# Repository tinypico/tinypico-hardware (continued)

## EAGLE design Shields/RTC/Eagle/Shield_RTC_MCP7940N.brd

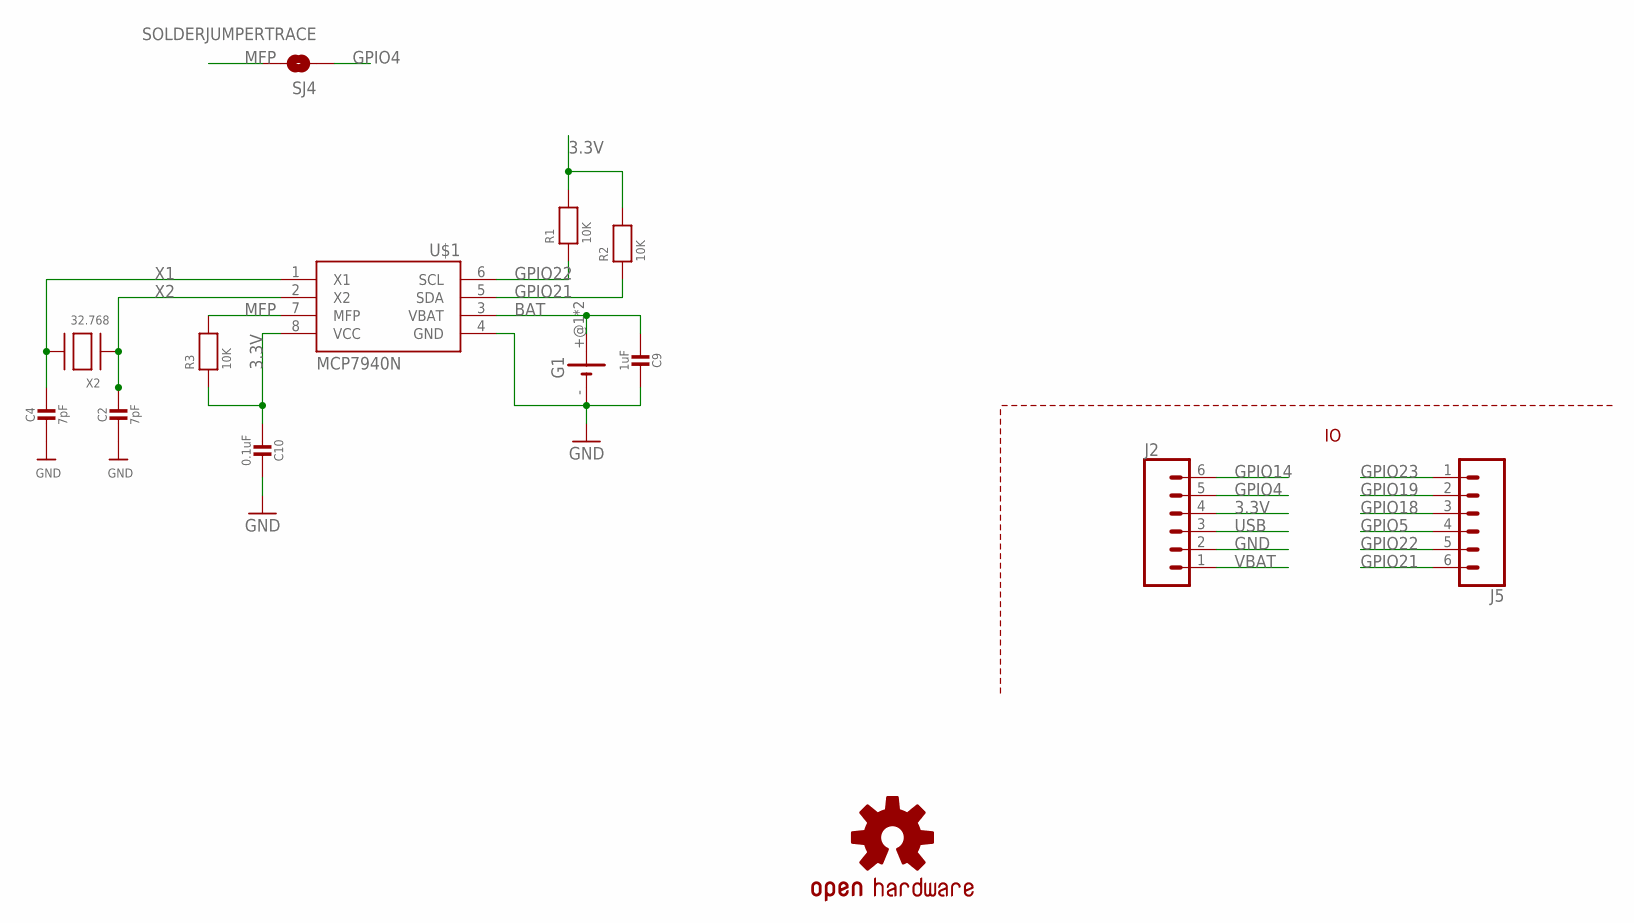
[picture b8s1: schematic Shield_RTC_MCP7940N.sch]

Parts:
C2, C4: 7pF; _0603MP
C9: 1uF; _0603MP
C10: 0.1uF; _0603MP
G1: 10MM_SM_COIN_CELL_CLIP
J2, J5: CONN_06NO_SILK_FEMALE_PTH; 1X06_NO_SILK
LOGO1: OSHW-LOGOS; OSHW-LOGO-S
R1, R2, R3: 10K; _0603MP
SJ4: SOLDERJUMPERTRACE; SPARKFUN_SJ_2S-TRACE
U$1: MCP7940N; SOIC8_150MIL
X2: 32.768; XTAL3215

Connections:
3.3V: C10.2, J2.4, R1.2, R2.2, R3.1, U$1.8 (VCC)
BAT: C9.2, G1.+@1 (+), G1.+@2 (+), U$1.3 (VBAT)
GND: C2.2, C4.2, C9.1, C10.1, G1.-, J2.2, U$1.4 (GND)
GPIO4: J2.5, SJ4.1
GPIO5: J5.4
GPIO14: J2.6
GPIO18: J5.3
GPIO19: J5.2
GPIO21: J5.6, R2.1, U$1.5 (SDA)
GPIO22: J5.5, R1.1, U$1.6 (SCL)
GPIO23: J5.1
MFP: R3.2, SJ4.2, U$1.7 (MFP)
USB: J2.3
VBAT: J2.1
X1: C4.1, U$1.1 (X1), X2.P$2
X2: C2.1, U$1.2 (X2), X2.P$1

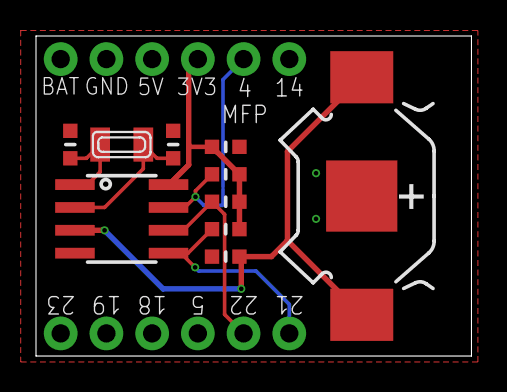
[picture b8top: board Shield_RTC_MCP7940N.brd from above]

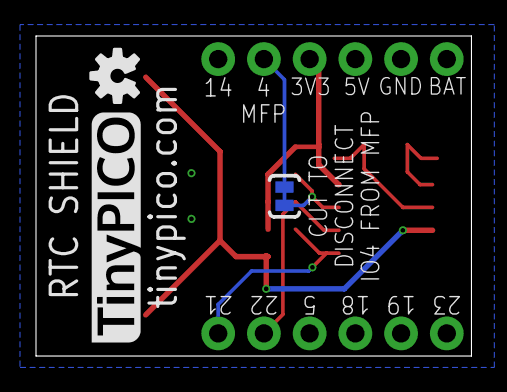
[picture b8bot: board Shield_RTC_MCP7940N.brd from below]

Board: 2 copper layers, 24.2 x 17.8 mm, 14 parts (2 on the bottom side), 9 nets.

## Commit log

2019-06-05 Fixed PSRAM silk no back of the bopard Fixed positions of the Inductor and Cap on the matching network Updated schematic PDF
2019-08-04 Added extra readmes to shields and empty template folders, re-stating the branding and open source requirements for using these files.
2019-08-04 Added missing license files
2019-08-06 Updated readme and removed TinyPICO logo from shield template
2020-06-25 Added Colour IPS Display Shield files <- Finally!
2020-08-03 Added TinyPICO NANO folder with footprints for various ECAD apps
2020-09-06 Replaced Altium footprint
    this one is also compatible with Circuit Studio
2021-02-01 Added TinyPICO Nano Schematic PDF
2021-02-01 Added TinyPICO V2 PDF Schematics for Micro-B and USB-C
2021-02-16 Added TinyPICO Nano KiCAD Eschema symbol
2021-03-15 Added TinyPICO USB-C STL file and updated some readme files
2021-05-21 Added TinyPICO NANO STL & STEP Added TinyPICO USB-C STL Renamed folder to 3D files
2021-05-29 Added TinyPICO Nano KiCad 5 symbol & footprint Added TinyPICO DipTrace ASCII files (thanks airheadbit) Cleaned up folder structure
2021-07-22 Added the TinyPICO v2 fritzing part created by @askpatrickw
2022-03-03 Update TinyPICO Nano Drawing.pdf
    - Added missing dimensions
    - Better alignment
2022-04-13 Added STL case files for Explorer Shield & Schematic
